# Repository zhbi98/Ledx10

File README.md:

# Ledx10

照明用 LED 驱动芯片驱动多颗 LED 时，连接方式需根据 LED 驱动芯片的类型（恒流源 or 恒压源）、输入电源电压（如 5V、12V、24V、AC-DC 等）以及单颗 LED 的正向压降（Vf，通常白光 LED 为 2.8V~3.6V）来决定。

## 1. LED 参数

工作电流（If）：20mA（指示灯），350mA/700mA/1A（照明级）。

单颗 LED 正向压降（Vf）：3.0V ~ 3.4V。

## 2. 连接

优先串联，大多数专用 **LED 恒流驱动芯片**（如 LM3409、AL8860、PT4115、TLD5098 等）设计用于 **驱动串联 LED 串**。

因为：恒流源要求负载为单一电流路径。串联可保证每颗 LED 电流一致，亮度均匀。无电流分配不均问题。

## 3. 分组

串联连接时，点数越多要求 LED 驱动芯片输出的电压越高，若电压不够，可以选用 **升压型 LED 恒流驱动芯片**，既安全又高效。但是升压型驱动芯片的电压也不是无限的，当 LED 串联总电压高于驱动芯片最大设计输出电压时可以按串并联进行分组设计。

例如：有 10 颗 LED，若驱动芯片最大设计输出电压为 **24V**，最多支持：24V ÷ 3.2V ≈ **7 颗串联**，此时必须按照串联和并联组合重新分组。

**输出电压 12V：**

2 串 × 5 并（即 2 串，每串 5 颗），每串压降 ≈ 16V，不可行（超压） 。

5 串 × 2 并（即 5 串，每串 2 颗）每串压降 ≈ 6.4V，总电流 = 2×If ，可行（需恒流+均流）。

**输出电压 24V：**

3 串 × 3+1（即 3 串，每串 3 颗，和一颗并联） 不均衡（避免）。

2 串 × 5 颗（即 2 串，每串 5 颗），每串 5×3.2=16V < 24V（最佳）。

**输出电压 36V：**

1 串 × 10 颗，压降≈32V < 36V，最理想。

**结论：**

若有 ≥36V 电源 10 颗全串联最佳，若只有24V 电源 2 串，每串 5 颗，若只有 12V 电源 5 串，每串 2 颗（但需注意并联均流）。

### 注意

连接照明 LED 的核心原则就是：尽可能将 LED 串联成单串（或少数几串），确保每串电流一致，避免并联不均流问题。

串联和并联组合时要用相同型号的 LED 并联，不能简单并联（恒流源并联会导致电流分配不均，部分 LED 过流烧毁），两串 Vf 略有差异，电流全走 Vf 小的一路导致另一路不亮或亮度极低，此路过流。

## 4. 驱动芯片

10 颗串联（32V@350mA），**降压（Buck）恒流**（如 PT4115，输入 >36V）。

12V 输入 → 驱动 10 颗，**升压（Boost）恒流**（如 AL8861、MT7201）。

多串并联（如 2×5），带多路输出或外接 MOSFET 的恒流 IC。

根据 LED 驱动芯片的输出电压来决定 LED 如何分组，最优解是选择是全串联 + 恒流驱动，若电压不够，**不要强行并联**，而是选用 **升压型 LED 恒流驱动芯片**，既安全又高效。

## 5. 单点失效

一颗 LED 开路（损坏/虚焊/断线）整串熄灭，这在照明应用中确实是个关键可靠性问题。尽管有 “单点失效” 风险，串联仍是恒流驱动下的首选。

因为：电流绝对一致，所有 LED 亮度均匀，无有的亮、有的暗。驱动电路简单，单路恒流即可，成本低、效率高。无热失控风险，并联时 Vf 低的 LED 会抢电流导致过热从而更抢流最终烧毁。

工程上已有成熟方案来平衡串联的电流一致性优势和单点故障风险，所以不是不用串联，而是要防止单点失效或容忍失效。

### 旁路器件

每颗 LED 并联一个 LED 专用旁路二极管或齐纳二极管（Zener）。

**原理：**

当某颗 LED 开路时，其两端电压急剧升高 → 触发并联的保护器件导通 → 电流绕过坏掉的 LED，其余继续工作。

**注意**：

齐纳电压需满足 V_Z > V_f ， V_Z < 驱动芯片最大耐压 / 10，正常时不导通。例如 Vf=3.2V → 选 5.6V 齐纳（常见且安全）。

**缺点：** 

成本略增（10 颗 LED 多 10 个二极管），坏一颗后，总电压下降 ≈3.2V，电流可能微升（但恒流芯片会自动调整）。

### 分组串联

将 10 颗分为 **2 组 × 5 串**（或其他组合），使用 **双通道恒流驱动芯片**（如 TLC5916、AL8805、CAT4101×2）。

一组坏了，另一组仍亮（50% 亮度维持），适用于 **不能容忍全灭** 的场景（如汽车灯、应急照明）。缺点是成本高、电路复杂。

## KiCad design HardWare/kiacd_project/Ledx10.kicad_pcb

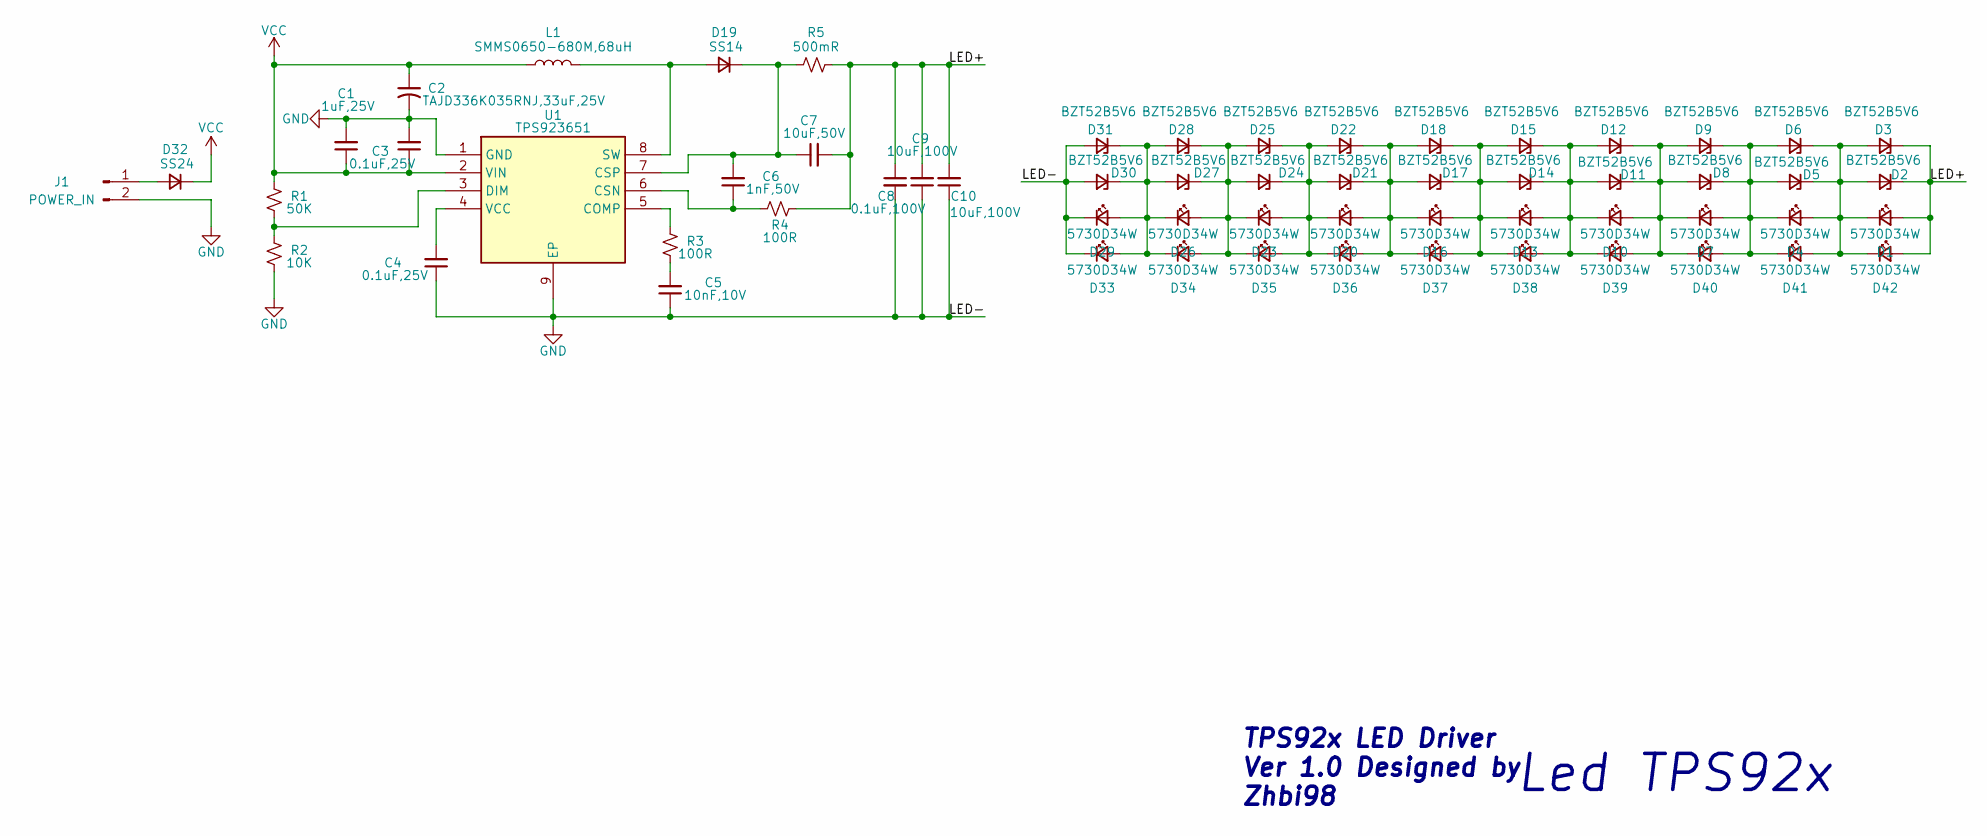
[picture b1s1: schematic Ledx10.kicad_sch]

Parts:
C1: 1uF,25V; C_0805_2012Metric
C2: TAJD336K035RNJ,33uF,25V; CP_EIA-7343-31_Kemet-D
C3, C4: 0.1uF,25V; C_0805_2012Metric
C5: 10nF,10V; C_0805_2012Metric
C6: 1nF,50V; C_0805_2012Metric
C7: 10uF,50V; C_0805_2012Metric
C8: 0.1uF,100V; C_0805_2012Metric
C9, C10: 10uF,100V; C_1206_3216Metric
D1, D4, D7, D10, D13, D16, D20, D23, D26, D29, D33, D34, D35, D36, D37, D38, D39, D40, D41, D42: 5730D34W; LED5730_2012Metric
D2, D3, D5, D6, D8, D9, D11, D12, D14, D15, D17, D18, D21, D22, D24, D25, D27, D28, D30, D31: BZT52B5V6; D_SOD-123
D19: SS14; D_SMA
D32: SS24; D_SMA
J1: POWER_IN; WIRE-TH_1x2P-P4.0_L6.5-W4.0
L1: SMMS0650-680M,68uH; L_6.3x6.3_H3
R1: 50K; R_0805_2012Metric
R2: 10K; R_0805_2012Metric
R3, R4: 100R; R_0805_2012Metric
R5: 500mR; R_1206_3216Metric
U1: TPS923651; WSON-8_L2.0-W2.0-P0.5_TPS923651

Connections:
/LED+: C7.2, C8.1, C9.2, C10.2, D1.2 (A), D2.1 (K), D3.1 (K), D42.2 (A), R4.2, R5.2
GND: C1.2, C2.2, C3.2, C4.1, C5.1, C8.2, C9.1, C10.1, D29.1 (K), D30.2 (A), D31.2 (A), D33.1 (K), J1.2, R2.1, U1.1 (GND), U1.9 (EP)
unnamed: C5.2, R3.1
unnamed: D1.1 (K), D2.2 (A), D3.2 (A), D4.2 (A), D5.1 (K), D6.1 (K), D41.2 (A), D42.1 (K)
unnamed: D4.1 (K), D5.2 (A), D6.2 (A), D7.2 (A), D8.1 (K), D9.1 (K), D40.2 (A), D41.1 (K)
unnamed: D7.1 (K), D8.2 (A), D9.2 (A), D10.2 (A), D11.1 (K), D12.1 (K), D39.2 (A), D40.1 (K)
unnamed: D10.1 (K), D11.2 (A), D12.2 (A), D13.2 (A), D14.1 (K), D15.1 (K), D38.2 (A), D39.1 (K)
unnamed: D13.1 (K), D14.2 (A), D15.2 (A), D16.2 (A), D17.1 (K), D18.1 (K), D37.2 (A), D38.1 (K)
unnamed: D16.1 (K), D17.2 (A), D18.2 (A), D20.2 (A), D21.1 (K), D22.1 (K), D36.2 (A), D37.1 (K)
unnamed: D19.2 (A), L1.2, U1.8 (SW)
unnamed: C6.2, C7.1, D19.1 (K), R5.1, U1.7 (CSP)
unnamed: D20.1 (K), D21.2 (A), D22.2 (A), D23.2 (A), D24.1 (K), D25.1 (K), D35.2 (A), D36.1 (K)
unnamed: D23.1 (K), D24.2 (A), D25.2 (A), D26.2 (A), D27.1 (K), D28.1 (K), D34.2 (A), D35.1 (K)
unnamed: D26.1 (K), D27.2 (A), D28.2 (A), D29.2 (A), D30.1 (K), D31.1 (K), D33.2 (A), D34.1 (K)
unnamed: D32.2 (A), J1.1
unnamed: R3.2, U1.5 (COMP)
unnamed: C6.1, R4.1, U1.6 (CSN)
unnamed: R1.1, R2.2, U1.3 (DIM)
unnamed: C4.2, U1.4 (VCC)
VCC: C1.1, C2.1, C3.1, D32.1 (K), L1.1, R1.2, U1.2 (VIN)

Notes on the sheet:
TPS92x LED Driver Ver 1.0 Designed by Zhbi98
Led TPS92x

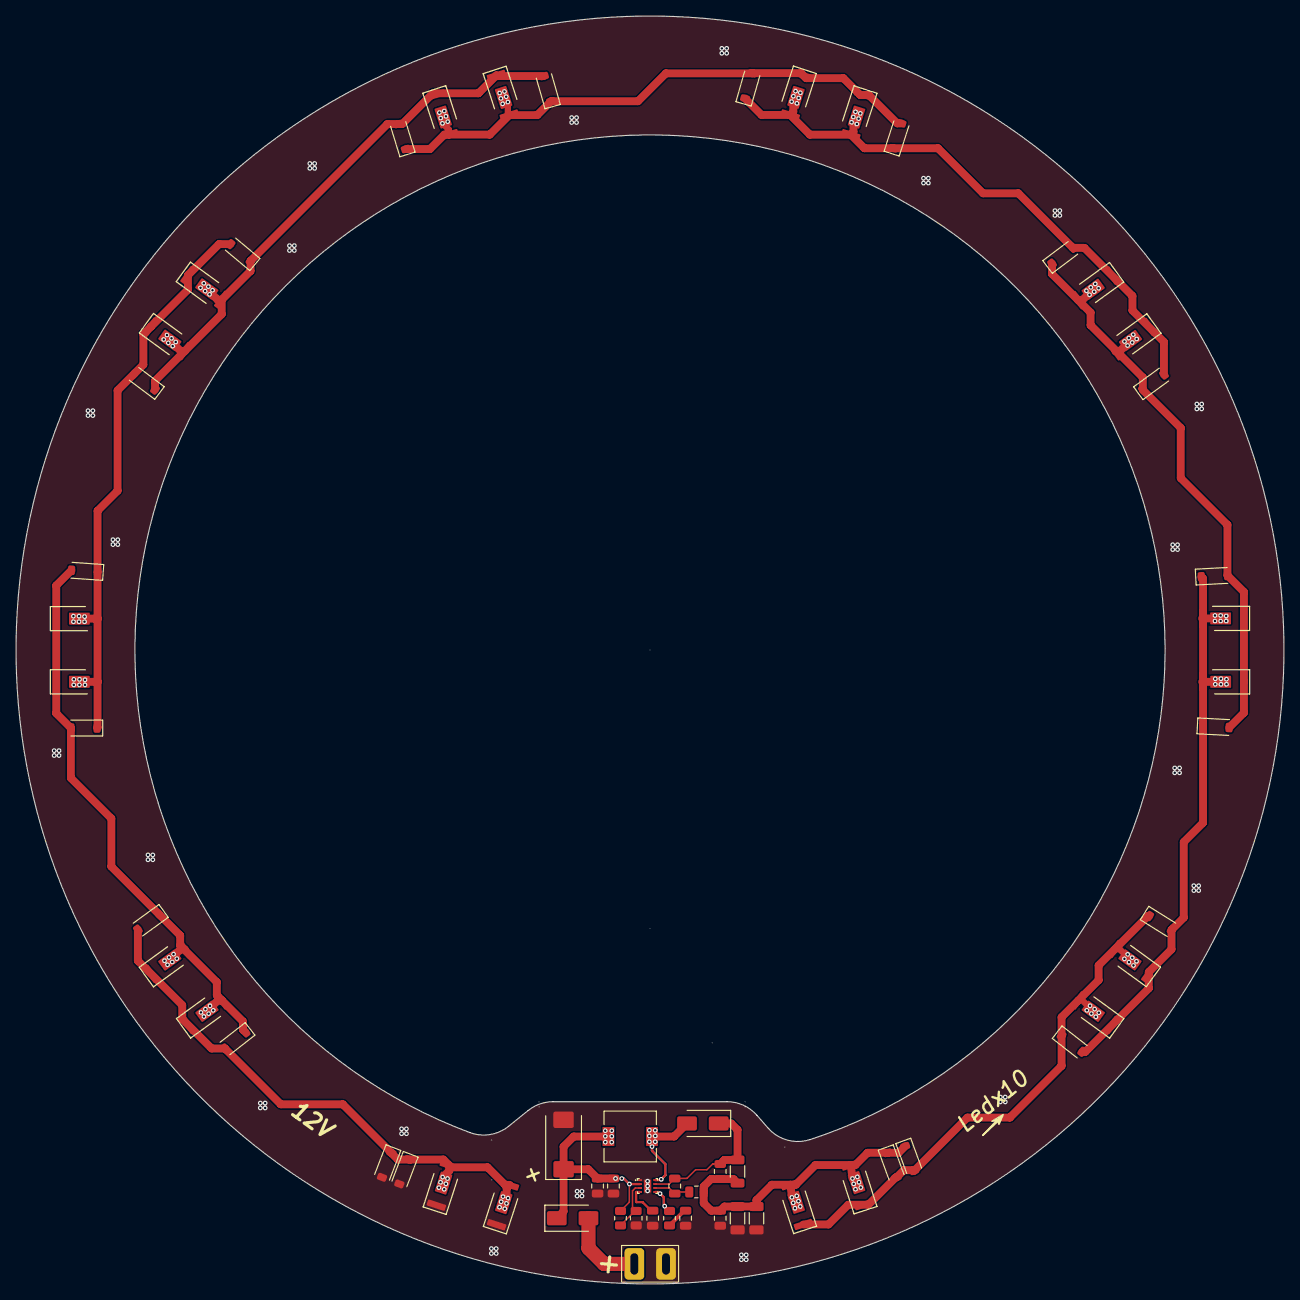
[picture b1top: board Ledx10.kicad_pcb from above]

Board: 2 copper layers, 160.0 x 160.0 mm, 60 parts (0 on the bottom side), 20 nets.

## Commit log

2026-01-19 添加数据手册
2026-01-19 更新 PCB 铺铜，和泪滴
2026-01-20 更新电路设计LED增加到20pix
2026-01-21 更新PCB设计，增加LED并联，增强光照强度
2026-02-07 更新LED5730封装错误，手册没有说明散热焊盘与阳极相连
2026-02-27 更新设计方案
